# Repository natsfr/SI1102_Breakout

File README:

Quick little breakout board for SI1102.
Can use external LED  and External settings
for threshold.

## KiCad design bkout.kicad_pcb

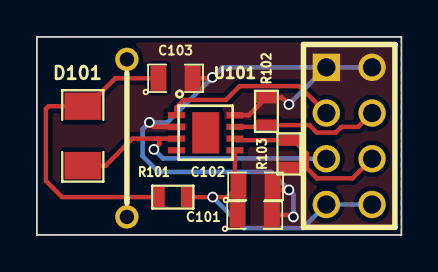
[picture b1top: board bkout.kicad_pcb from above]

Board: 2 copper layers, 20.2 x 11.0 mm, 9 parts (0 on the bottom side), 7 nets.

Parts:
C101, C102, C103: CAP_0805; SM0805
D101: Led_Small; SM1206
P101: CONN_02X04; pin_array_4x2
R101, R102, R103: RES_0603; SM0603
U101: SI1102; ODFN-8_3x3

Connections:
/FR: P101.4, R102.1, U101.7
/PRX: P101.3, U101.1
/SREN: P101.6, R103.1, U101.6
/TXO: D101.2, P101.5, U101.3
GND: C101.2, C102.2, C103.2, P101.1, P101.2, R102.2, R103.2, U101.2, U101.8
unnamed: C103.1, D101.1, R101.2
VCC: C101.1, C102.1, P101.7, P101.8, R101.1, U101.5

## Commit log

2015-08-03 First and last version :)
2015-08-03 Ajout de serigraphie pour Hugo qui râle :p
2015-08-04 Sent to seeedstudio
